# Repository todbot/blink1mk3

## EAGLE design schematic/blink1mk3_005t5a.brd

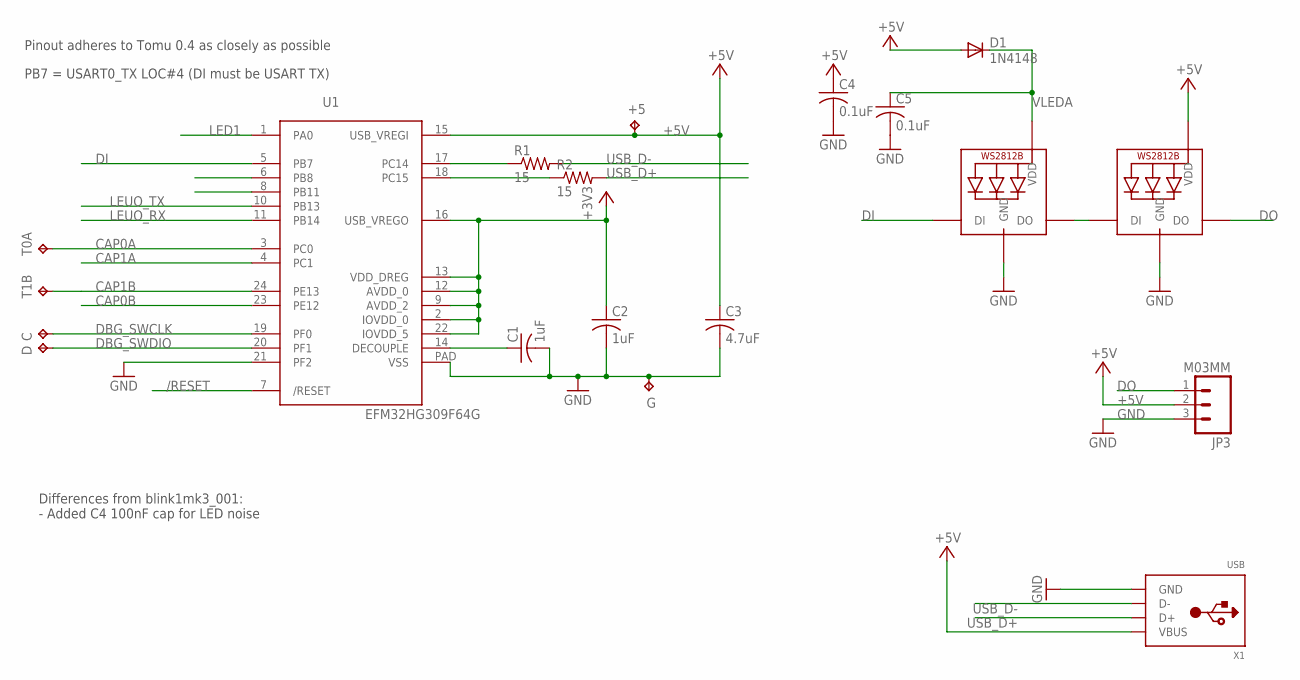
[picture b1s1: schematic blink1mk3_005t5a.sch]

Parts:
+5: TPTP10R; TP10R
C: TPTP10R; TP10R
C1, C2: 1uF; C0402
C3: 4.7uF; C0402
C4, C5: 0.1uF; C0402
D: TPTP10R; TP10R
D1: 1N4148; SOD523
G: TPTP10R; TP10R
JP3: M03MM; 1X03-1.5MM
LED1, LED2: SK6812MINI; LED3535
R1, R2: 15; R0402
T0A, T1B: TPTP15R; TP15R
U1: EFM32HG309F64G; QFN24PAD
X1: USB; MOLEX-48037-1000

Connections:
+3V3: C2.1, U1.2 (IOVDD_0), U1.9 (AVDD_2), U1.12 (AVDD_0), U1.13 (VDD_DREG), U1.16 (USB_VREGO), U1.22 (IOVDD_5)
+5V: +5.TP, C3.1, C4.1, D1.A, JP3.2, LED2.2 (VDD), U1.15 (USB_VREGI), X1.1 (VBUS)
/RESET: U1.7 (/RESET)
CAP0A: T0A.TP, U1.3 (PC0)
CAP0B: U1.23 (PE12)
CAP1A: U1.4 (PC1)
CAP1B: T1B.TP, U1.24 (PE13)
DBG_SWCLK: C.TP, U1.19 (PF0)
DBG_SWDIO: D.TP, U1.20 (PF1)
DECOUPLE: C1.1, U1.14 (DECOUPLE)
DI: LED1.1 (DI), U1.5 (PB7)
DO: JP3.1, LED2.3 (DO)
GND: C1.2, C2.2, C3.2, C4.2, C5.2, G.TP, JP3.3, LED1.4 (GND), LED2.4 (GND), U1.21 (PF2), U1.PAD (VSS), X1.4 (GND)
LED1: U1.1 (PA0)
LEUO_RX: U1.11 (PB14)
LEUO_TX: U1.10 (PB13)
unnamed: LED1.3 (DO), LED2.1 (DI)
RUSB_D+: R2.1, U1.18 (PC15)
RUSB_D-: R1.1, U1.17 (PC14)
USB_D+: R2.2, X1.3 (D+)
USB_D-: R1.2, X1.2 (D-)
VLEDA: C5.1, D1.C, LED1.2 (VDD)

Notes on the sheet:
PB7 = USART0_TX LOC#4 (DI must be USART TX)
Pinout adheres to Tomu 0.4 as closely as possible
Differences from blink1mk3_001: - Added C4 100nF cap for LED noise

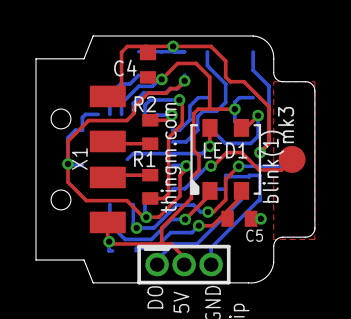
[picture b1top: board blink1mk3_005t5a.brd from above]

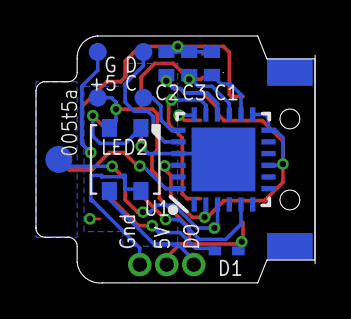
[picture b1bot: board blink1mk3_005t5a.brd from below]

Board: 2 copper layers, 15.5 x 13.7 mm, 19 parts (11 on the bottom side), 16 nets.

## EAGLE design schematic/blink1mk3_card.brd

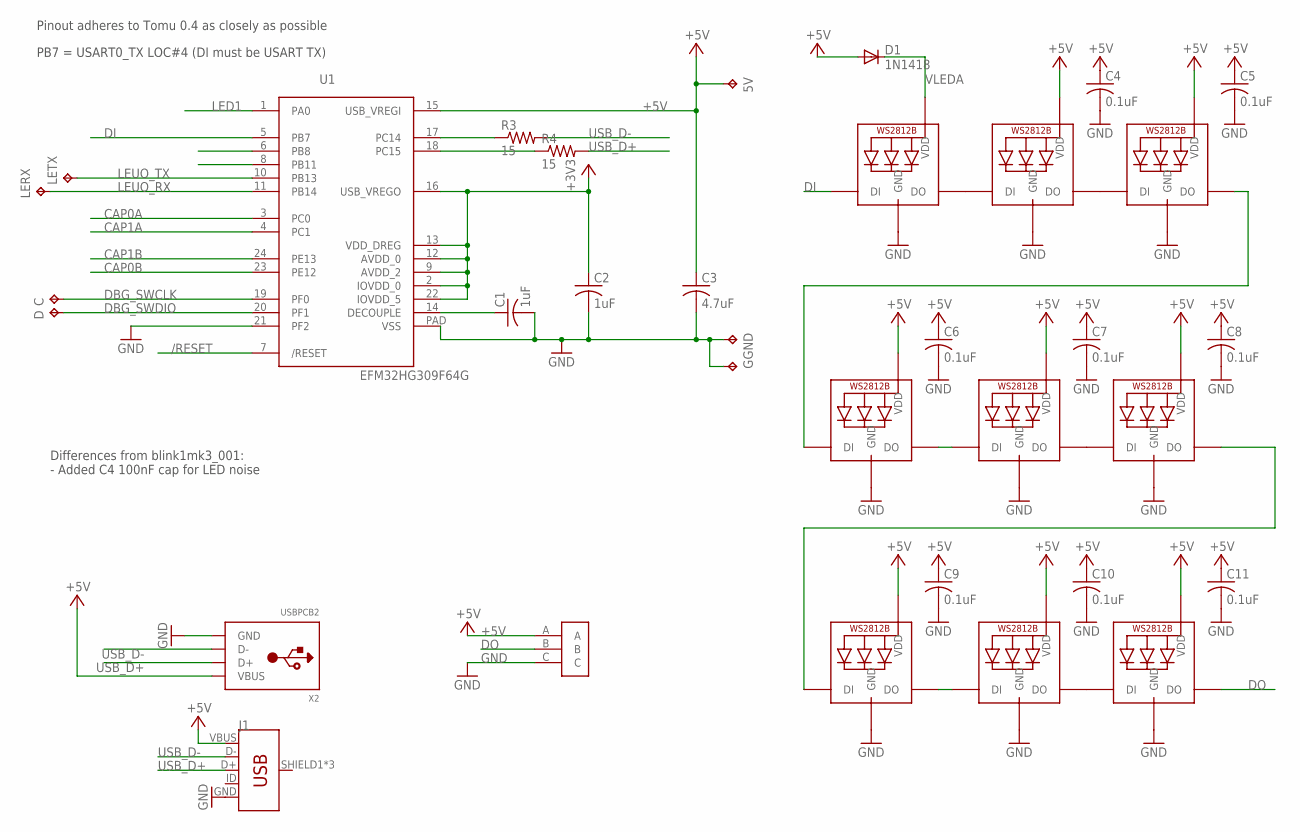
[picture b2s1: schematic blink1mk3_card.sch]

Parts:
5V: TPTP15R; TP15R
C: TPTP15R; TP15R
C1, C2: 1uF; C0603
C3: 4.7uF; C0603
C4, C5, C6, C7, C8, C9, C10, C11: 0.1uF; C0603
D: TPTP15R; TP15R
D1: 1N1418; SOD523
G: TPTP14SQ; TP14SQ
GND: TPTP14SQ; TP14SQ
J1: USB_MICRO-B_FEMALE-SMT; USB-B-MICRO-SMD
LED1, LED2, LED3, LED4, LED5, LED6, LED7, LED8, LED9: WS2812B3535; LED3535
LERX: TPTP15R; TP15R
LETX: TPTP15R; TP15R
R3, R4: 15; R0603
U1: EFM32HG309F64G; QFN24PAD
U$1: LED_STRIP_3P; LEDSTRIP-3P
X2: USBPCB2; USB-A-PCB-2

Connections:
+3V3: C2.1, U1.2 (IOVDD_0), U1.9 (AVDD_2), U1.12 (AVDD_0), U1.13 (VDD_DREG), U1.16 (USB_VREGO), U1.22 (IOVDD_5)
+5V: 5V.TP, C3.1, C4.1, C5.1, C6.1, C7.1, C8.1, C9.1, C10.1, C11.1, D1.A, J1.VBUS, LED2.2 (VDD), LED3.2 (VDD), LED4.2 (VDD), LED5.2 (VDD), LED6.2 (VDD), LED7.2 (VDD), LED8.2 (VDD), LED9.2 (VDD), U1.15 (USB_VREGI), U$1.A, X2.5V (VBUS)
/RESET: U1.7 (/RESET)
CAP0A: U1.3 (PC0)
CAP0B: U1.23 (PE12)
CAP1A: U1.4 (PC1)
CAP1B: U1.24 (PE13)
DBG_SWCLK: C.TP, U1.19 (PF0)
DBG_SWDIO: D.TP, U1.20 (PF1)
DECOUPLE: C1.1, U1.14 (DECOUPLE)
DI: LED1.1 (DI), U1.5 (PB7)
DO: LED9.3 (DO), U$1.B
GND: C1.2, C2.2, C3.2, C4.2, C5.2, C6.2, C7.2, C8.2, C9.2, C10.2, C11.2, G.TP, GND.TP, J1.GND, LED1.4 (GND), LED2.4 (GND), LED3.4 (GND), LED4.4 (GND), LED5.4 (GND), LED6.4 (GND), LED7.4 (GND), LED8.4 (GND), LED9.4 (GND), U1.21 (PF2), U1.PAD (VSS), U$1.C, X2.GND
LED1: U1.1 (PA0)
LEUO_RX: LERX.TP, U1.11 (PB14)
LEUO_TX: LETX.TP, U1.10 (PB13)
unnamed: LED1.3 (DO), LED2.1 (DI)
unnamed: LED7.3 (DO), LED8.1 (DI)
unnamed: LED4.3 (DO), LED5.1 (DI)
unnamed: LED5.3 (DO), LED6.1 (DI)
unnamed: LED2.3 (DO), LED3.1 (DI)
unnamed: LED3.3 (DO), LED4.1 (DI)
unnamed: LED8.3 (DO), LED9.1 (DI)
unnamed: LED6.3 (DO), LED7.1 (DI)
RUSB_D+: R4.1, U1.18 (PC15)
RUSB_D-: R3.1, U1.17 (PC14)
USB_D+: J1.D+, R4.2, X2.USB_P (D+)
USB_D-: J1.D-, R3.2, X2.USB_M (D-)
VLEDA: D1.C, LED1.2 (VDD)

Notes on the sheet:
PB7 = USART0_TX LOC#4 (DI must be USART TX)
Pinout adheres to Tomu 0.4 as closely as possible
Differences from blink1mk3_001: - Added C4 100nF cap for LED noise

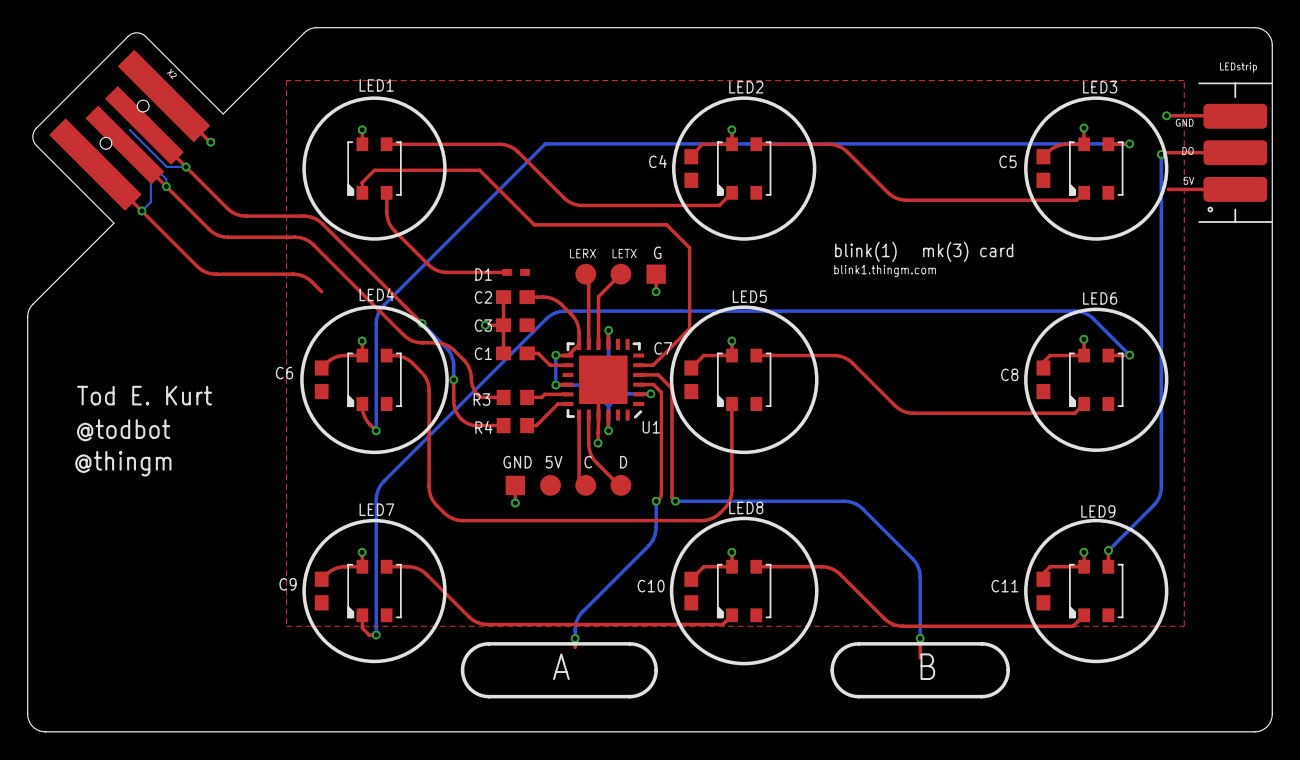
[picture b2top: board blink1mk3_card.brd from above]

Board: 2 copper layers, 89.8 x 50.8 mm, 34 parts (1 on the bottom side), 23 nets.

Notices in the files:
parts and their libraries:
SparkFun-Connectors: Licensing: Creative Commons ShareAlike 4.0 International - https://creativecommons.org/licenses/by-sa/4.0
